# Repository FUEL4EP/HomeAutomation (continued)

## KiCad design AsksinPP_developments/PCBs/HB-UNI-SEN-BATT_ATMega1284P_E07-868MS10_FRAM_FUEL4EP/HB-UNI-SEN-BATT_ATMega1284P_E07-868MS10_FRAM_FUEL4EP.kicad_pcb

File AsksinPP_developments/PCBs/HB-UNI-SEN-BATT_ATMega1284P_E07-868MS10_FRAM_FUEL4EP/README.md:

# HB-UNI-SEN-BATT_ATMega1284P_E07-868MS10_FRAM_FUEL4EP ](https://creativecommons.org/licenses/by-nc-sa/4.0/)  

**Platine für DIY AsksinPP für**
- eingebauter SMD TQFP-44 [ATMega1284P](https://ww1.microchip.com/downloads/en/DeviceDoc/doc8059.pdf) mit 128kByte Programmspeicher, 16kByte SRAM, 4kByte EEPROM
- [eByte E07-868MS10 Sendemodul](https://www.rcscomponents.kiev.ua/datasheets/e07-868ms10_usermanual_en_v1_20.pdf)
- Bestückungsoption für [Waveshare ePaper Modul (1.54inch (B)](https://www.waveshare.com/product/1.54inch-e-paper-module.htm)
- Bestückungsoption für [TPS61221 Aufwärtswandler](https://www.ti.com/lit/ds/symlink/tps61221.pdf?ts=1634546965861&ref_url=https%253A%252F%252Fwww.ti.com%252Fproduct%252FTPS61221) bei NiMH Akkumulatorbetrieb
- Bestückungsoption für 2x 2Mbit (256k x 8Bit) SPI FRAM MB85RS2MTPF-G-JNERE2 für die Speicherung von Temperaturdaten für die online-Berechnung von gleitenden Mittelwerten bis zu einem Jahr (365 Tage)
- alle SMD Bausteine sind mit dem JLCPCB SMT Bestückungsservice kostengünstig und qualitativ hochwertig bestückbar, das ist also auch für Grobmotoriker wie mich gegeignet :-)

## Credits

- diese Platine ist ursprünglich von Alexander Reinerts Platine [HB-UNI-SEN-BATT](https://github.com/alexreinert/PCB/tree/master/HB-UNI-SEN-BATT) abgeleitet, aber in vielerlei Hinsicht verbessert
- vielen Dank an Alexander Reinert für die Vorarbeit.

## Platine Version 1.1 wurde nach Fertigung bei JLCPCB erfolgreich validiert

- Version 1.1 wurde entwickelt mit KiCAD 5.1.12  
- für KiCAD 6 wurde eine Migration auf Version 1.2 durchgeführt
- Prototyp Version 1.1 erfolgreich  bei JLCPCB gefertigt und validiert
- Software ist noch in Entwicklung, siehe unten
- Bilder der Prototyp-Platinen, die bei JLCPCB gefertigt wurden:

- die nicht SMD Bauteile müssen von Hand verlötet werden
- weitere Infos per PN bei [FUEL4EP](https://homematic-forum.de/forum/ucp.php?i=pm&mode=compose&u=20685) im Homematic Forum.

## Eigenschaften

- abgeleitet aus [HB-UNI-SEN-BATT](https://github.com/alexreinert/PCB/tree/master/HB-UNI-SEN-BATT)
- kompletter Datensatz für KiCAD 6 auf Github verfügbar::
    + 'git clone https://github.com/FUEL4EP/HomeAutomation.git' oder als [ZIP-Datei](https://github.com/FUEL4EP/HomeAutomation/archive/refs/heads/master.zip)
    + die Platinendaten sind dann unter 'HomeAutomation/AsksinPP_developments/PCBs/HB-UNI-SEN-BATT_ATMega1284P_E07-868MS10_FRAM_FUEL4EP' direkt mit KiCAD aufrufbar
- neue Eigenschaften:
    + SMD Bestückung, wo möglich
    + SMD TQFP-44 [ATMega1284P](https://ww1.microchip.com/downloads/en/DeviceDoc/doc8059.pdf) mit 128kByte Programmspeicher, 16kByte SRAM, 4kByte EEPROM
    + Bestückungsoption für [Waveshare ePaper Modul (1.54inch (B)](https://www.waveshare.com/product/1.54inch-e-paper-module.htm)
    + Bestückungsoption für [TPS61221 Aufwärtswandler](https://www.ti.com/lit/ds/symlink/tps61221.pdf?ts=1634546965861&ref_url=https%253A%252F%252Fwww.ti.com%252Fproduct%252FTPS61221) bei NiMH Akkumulatorbetrieb
    + Bestückungsoption für 2x 2Mbit (256k x 8Bit) SPI FRAM MB85RS2MTPF-G-JNERE2 für die Speicherung von Temperaturdaten für die online-Berechnung von gleitenden Mittelwerten bis zu einem Jahr (365 Tage)
    + alle SMD Bausteine sind mit dem JLCPCB SMT Bestückungsservice kostengünstig und qualitativ hochwertig bestückbar, das ist also auch für Grobmotoriker wie mich gegeignet :-)
    + Stiftleiste J10 mit Versorgungspannungen zum Gehäuseoberteil oder Akkulademodul
    + dedizierte passende Stiftleisten für verschiedene Sensoren / Sensorbreakouts
        * J6: SHT75, SHT85
        * J7: AHT15, AHT25
        * J8: AHT20+BMP280 Breakout (z.B. [eBay](https://www.ebay.de/itm/174883359464)
        * J9: BME280/BMP280 Breakout
        * J13: BME680 Breakout (Pimoroni)
    + Korrektur der Abstandfehlers bei einem Batteriehalter. Beim [HB-UNI-SEN-BATT](https://github.com/alexreinert/PCB/tree/master/HB-UNI-SEN-BATT) hat das schon mal gerne zu thermischen Ausfällen durch mechanische Spannungen geführt.
    + als Funkmodul wird das [eByte E07-868MS10 Sendemodul](https://www.rcscomponents.kiev.ua/datasheets/e07-868ms10_usermanual_en_v1_20.pdf) verwendet. Dieses ist qualitativ viel besser als die üblichen grünen noname 868 MHz Funkmodule.
    + das schafft Platz für eine 8-polige Stiftleiste J11 zum optionalen Anschluss eines [Waveshare ePaper Moduls (1.54inch (B)](https://www.waveshare.com/product/1.54inch-e-paper-module.htm). Der ATMega1284P hat auch genügend RAM für die Programmierung eines 200 Pixel x 200 Pixel e-Papermoduls.
    + JLCPCB BOM and CPL Dateien für SMT Service werden [bereitgestellt](./jlcpcb/production_files)
- Hinweis: der MB85RS2MTPF FRAM Speicher muss bei JLCPCB als [Vorbestellung von Bauteilen](https://support.jlcpcb.com/article/164-what-is-jlcpcb-parts-pre-order-service) vorab gekauft werden

### Benötigte Bauteile:

- bedingt durch die SMT Service von JLCPCB sind nur noch wenige Durchsteckbauteile von Hand zu verlöten:
* [eByte E07-868MS10 Sendemodul 868MHz](https://www.elecbee.com/de-24376-E07-868MS10-CC1101-Stamp-Hole-Antenna-IoT-UHF-1000m-868MHz-SPI-10dBm-Wireless-Transmitter-Transceiver-RF-Module) oder alternativ das [Elecbee CC1101 Wireless-Modul 868 MHz](https://www.elecbee.com/de-24507-CC1101-Wireless-Module-868MHz-Digital-Transmission-Receiving-Industrial-grade-RF-Communication-Transparent-Transmission) Modul
* e-Paper [Waveshare ePaper Moduls (1.54inch (B)](https://www.waveshare.com/product/1.54inch-e-paper-module.htm) (optional, Anschluss an J11)
* 2x Keystone 2460 Batteriehalter 1xAA
* Stiftleiste RM 1.27mm 1x8 Pin (für eByte E07-868MS10 Sendemodul 868MHz)
* Stiftleiste RM 2mm 1x8 Pin (für ePaper)
* Stiftleisten RM 2,54mm (nach Bedarf)
* IRLU024N (optional für Verpolungsschutz)
* Versorgung durch NiMH Akkumulatoren und Aufwärtswandler ist vorbereitet (JP2)
* Bestückungsoption Aufwärtswandler siehe [Schaltplan](Schematics/HB-UNI-SEN-BATT_ATMega1284P_E07-868MS10_FUEL4EP.pdf), unter KiCAD sind alle Referenzen eingetragen

### Aufbauhinweise

- es wird dringend angeraten, vor dem Einbau der I2C Sensoren durchzuführen
    + einen Frequenztest. Hier der Frequenztest für einen ATmega 1284p : [FreqTest_1284P.ino](../Supplements/FreqTest_1284P/FreqTest_1284P.ino)
    + einen Leckagetest. Hier der Leckagetest für einen ATmega 1284p : [SleepTest_1284P.ino](../Supplements/SleepTest_1284P/SleepTest_1284P.ino)
        + der Leckagestrom im Sleepmode sollte < 10 uA betragen

### Passende AsksinPP Projekte von FUEL4EP
- eine passende Arduino FRAM Bibliothek ist [hier](../../sketches/HB-UNI-Sensor1-THP_MA-AHT20_BMP280/Sensors/Fujitsu_MB85RS2MTPF_FRAM_circular_buffer.h)
	* diese FRAM Bibliothek wird beim Sketch [HB-UNI-Sensor1-THP_MA-AHT20_BMP280](https://github.com/FUEL4EP/HomeAutomation/tree/master/AsksinPP_developments/sketches/HB-UNI-Sensor1-THP_MA-AHT20_BMP280) verwendet
- THP Sensor mit gleitender Mittelwertbildung der gemessenen Temperatur über 24 Stunden, 1 Woche, 1 Monat und 1 Jahr:
	* [HB-UNI-Sensor1-THP_MA-AHT20_BMP280](https://github.com/FUEL4EP/HomeAutomation/tree/master/AsksinPP_developments/sketches/HB-UNI-Sensor1-THP_MA-AHT20_BMP280)
		* alle Funktionen sind erfolgreich getestet, das FRAM funktioniert
		* damit lassen sich lokale Klimaschwankungen gut erfassen
		* der Sensor läuft bereits seit mehreren Monaten
- [HB-UNI-Sensor1-AQ-BME680](https://github.com/FUEL4EP/HomeAutomation/tree/master/AsksinPP_developments/sketches/HB-UNI-Sensor1-AQ-BME680)
- [HB-UNI-Sensor1-AQ-BME680_KF](https://github.com/FUEL4EP/HomeAutomation/tree/master/AsksinPP_developments/sketches/HB-UNI-Sensor1-AQ-BME680_KF)
- [HB-UNI-Sensor1-AQ-BME680_KF_DEBUG](https://github.com/FUEL4EP/HomeAutomation/tree/master/AsksinPP_developments/sketches/HB-UNI-Sensor1-AQ-BME680_KF_DEBUG)
- [HB-UNI-Sensor1-RAD-AL53](https://github.com/FUEL4EP/HomeAutomation/tree/master/AsksinPP_developments/sketches/HB-UNI-Sensor1-RAD-AL53)
- [HB-UNI-Sensor1-THP-SHT85](https://github.com/FUEL4EP/HomeAutomation/tree/master/AsksinPP_developments/sketches/HB-UNI-Sensor1-THP-SHT85)
- [HB-UNI-Sensor1-THP-SHT45_BME280](https://github.com/FUEL4EP/HomeAutomation/tree/master/AsksinPP_developments/sketches/HB-UNI-Sensor1-THP-SHT45_BME280)

### Notwendige Änderung der Betriebsspannungsmessung in Sketchen
- da die Platine einen fest verdrahteten Spannungsteiler R7 und R8 für die Betriebsspannung / Akkuspannungsmessung verwendet, muss in Sketchen folgende Anpassung gegebenenfalls durchgeführt werden:

- nur notwendig, wenn die Akkuspannung / Betriebsspannung größer als 3,5 Volt ist ( 2x AA Alkaline Batterie)

- von bisher
```
// 1) Standard: tmBattery, UBatt = Betriebsspannung AVR
#define BAT_SENSOR tmBattery
```
- nach
```
// 2) für StepUp/StepDown: tmBatteryResDiv, sense pin PA0 (=pin 37), activation pin PB3 (=pin 43) , Faktor = Rges/Rlow*1000, z.B. (100kOhm+47kOhm/100kOhm), Faktor (147k)/(100k)*1000 = 1470 (ATMega1284P)
// start with Faktor = 1470
// check in serial monitor the reported V2='accumulator voltage(MCU ADC) (x1000.0)' and compare with the reported V1='accumulator batteries voltage (x1000.0)'
// calculate voltage correction factor V1/V2
// calculate total Faktor = 1470 * V2/V1 = 1470 * 3141 / 3157 = 1463
#define BAT_SENSOR tmBatteryResDiv<A0, PB3, 1463>
```
- zur Berechnung von Faktor in tmBatteryResDiv wird ein Libreoffice Calc Sheet [tmBattery_tmBatteryResDiv_calculator.ods](../../tools/tmBattery_tmBatteryResDiv_calculator.ods) zur Verfügung gestellt
- in der Version 1.0 war R8 = 200kOhm, daher Faktor = 3000 (ohne Kalibrierung)
- in der Version 1.1 ist R8 = 47kOhm, daher Faktor = 1470 (ohne Kalibrierung)
### Anschluss eines FTDI Debuggers

- zum Anschluss eines FTDI Debuggers an die 6-polige Stiftleiste J12 bitte ein [6 Pin Dupontkabel 2.54mm Buchse-Buchse 20 cm](https://www.roboter-bausatz.de/p/6-pin-dupontkabel-2.54mm-buchse-buchse-20-cm) verwenden

### Passendes Gehäuse
* Camdenboss CBRS01SWH und CBRS01VWH
* oder [Gehäuse HB-UNI-SEN-BATT snap in V2 von wpatrick](https://www.thingiverse.com/thing:3540481) für 3D-Druck
* bei Einbau eines e-Paper Moduls muss das Gehäuseoberteil angepasst werden (noch zu tun)

### Hinweise
* Achtung: Kein Überspannungschutz vorhanden
* der Verpolungsschutz ist optional. Dafür Bauteil Q1 (IRLU024N) und R3 (100KOhm Widerstand) bestücken. Alternativ JP1 auf der Platinenrückseite brücken um ohne Verpolungsschutz zu arbeiten.
 * bei der Nutzung des JLCPCB SMT Bestückungsservice ist darauf zu achten, dass **alle** benötigten SMD Bauteile als im Lager **verfügbar** angezeigt werden. Sonst bitte **NICHT** bestellen! Gegebenenfalls müssen für die SMD-Widerstände äquivalente Widerstände von anderen Herstellern über die Suchfunktion ausgewählt werden.
 
## passende DIY AsksinPP Funkmodule 868,3 MHz für die Fertigung bei JLCPCB
- als DIY-Ersatz für das eByte E07 868M10S Funkmodul stehen zur Verfügung:
	-  [CC1101_868MHz_RF_Modul_FUEL4EP](https://github.com/FUEL4EP/HomeAutomation/tree/master/AsksinPP_developments/PCBs/CC1101_868MHz_RF_Modul_FUEL4EP) mit Drahtantenne
	- [CC1101_868MHz_UFL_RF_Modul_FUEL4EP](https://github.com/FUEL4EP/HomeAutomation/tree/master/AsksinPP_developments/PCBs/CC1101_868MHz_UFL_RF_Modul_FUEL4EP) mit U.FL Antennenbuchse
* alternativ für das Funkmodul eByte E07 868M10S kann der Adapter [Adapter_EByte_E07_900MM10S_to_Ebyte_E07_868MS10_FUEL4EP](https://github.com/FUEL4EP/HomeAutomation/tree/master/AsksinPP_developments/PCBs/Adapter_EByte_E07_900MM10S_to_Ebyte_E07_868MS10_FUEL4EP) bestückt mit einem Funkmodul eByte E07 900MM10S verwendet werden
	
## passende DIY I2C-Sensormodule für die Fertigung bei JLCPCB
- als DIY-Ersatz für kommerzielle Sensormodule stehen folgende passende Adapterplatinen zur Verfügung:
	- [I2C_Module_BME280_FUEL4EP](https://github.com/FUEL4EP/HomeAutomation/tree/master/AsksinPP_developments/PCBs/I2C_Module_BME280_FUEL4EP)
	- [I2C_Module_BME680_FUEL4EP](https://github.com/FUEL4EP/HomeAutomation/tree/master/AsksinPP_developments/PCBs/I2C_Module_BME680_FUEL4EP)
	- [I2C_Module_SHT85_BME280_FUEL4EP](https://github.com/FUEL4EP/HomeAutomation/tree/master/AsksinPP_developments/PCBs/I2C_Module_SHT85_BME280_FUEL4EP)
	- [I2C_Module_SHT45_BME280_FUEL4EP](https://github.com/FUEL4EP/HomeAutomation/tree/master/AsksinPP_developments/PCBs/I2C_Module_SHT45_BME280_FUEL4EP)
	- [4Bit_I2C_Port_Expander_Module_FUEL4EP](https://github.com/FUEL4EP/HomeAutomation/tree/master/AsksinPP_developments/PCBs/4Bit_I2C_Port_Expander_Module_FUEL4EP)

## Disclaimer

-   die Nutzung der hier veröffentlichten Inhalte erfolgt vollständig auf eigenes Risiko und ohne jede Gewähr.

## Versionsverlauf

-	V1.1 10. Jan 2022: R8 auf 47kOhm geändert, zusätzliche Aufdrucktexte
-   V1.1 10. Mai 2023: Prototypen von JLCPCB verfügbar, Systemvalidierung und Softwareentwicklung muss noch gemacht werden
-   V1.2 16. Jul 2023: Migration der Datenbasen zu KiCAD 6; als Induktivität    	                     für den Aufwärtswandler wird nun LQH3NPN4R7MM0L von
                         Murata Electronics verwendet, die bei JLCPCB bestellbar ist  (eventuell ist eine Vorbestellung notwendig) 
-   V1.3 14. Jul 2023: KiCAD 6 bedingte Verbesserungen der Datenbasis
-   V1.4 15. Aug 2023: Fix of EN pin of TPS61221 boost converter (must be tied to VIN)
-   S V1.5 17. Feb 2024: Fix of LCSC-Nummer von R7 (Fehler bei KiCAD 6 Migration) und KiCAD 6-Bibliothekspfad
-   S V1.6 26. Sep 2024: Migration auf KiCAD 8; Fix of LCSC-Nummern (R2,R4,R5)
-   L V1.5 26. Sep 2024: Migration auf KiCAD 8; Fix of LCSC-Nummern (R2,R4,R5) 
- KiCad Schaltplan-Editor Version: 8.0.5-8.0.5-0~ubuntu22.04.1, release build unter Kubuntu22.04.1
- KiCad Leiterplatteneditor Version: 8.0.5-8.0.5-0~ubuntu22.04.1, release build unter Kubuntu22.04.1 1.
- PCB Version 1.5
- Schematics  1.6

## Lizenz 

**Creative Commons BY-NC-SA**<br>
Give Credit, NonCommercial, ShareAlike

<br />This work is licensed under a <a rel="license" href="http://creativecommons.org/licenses/by-nc-sa/4.0/">Creative Commons Attribution-NonCommercial-ShareAlike 4.0 International License</a>.

-EOF

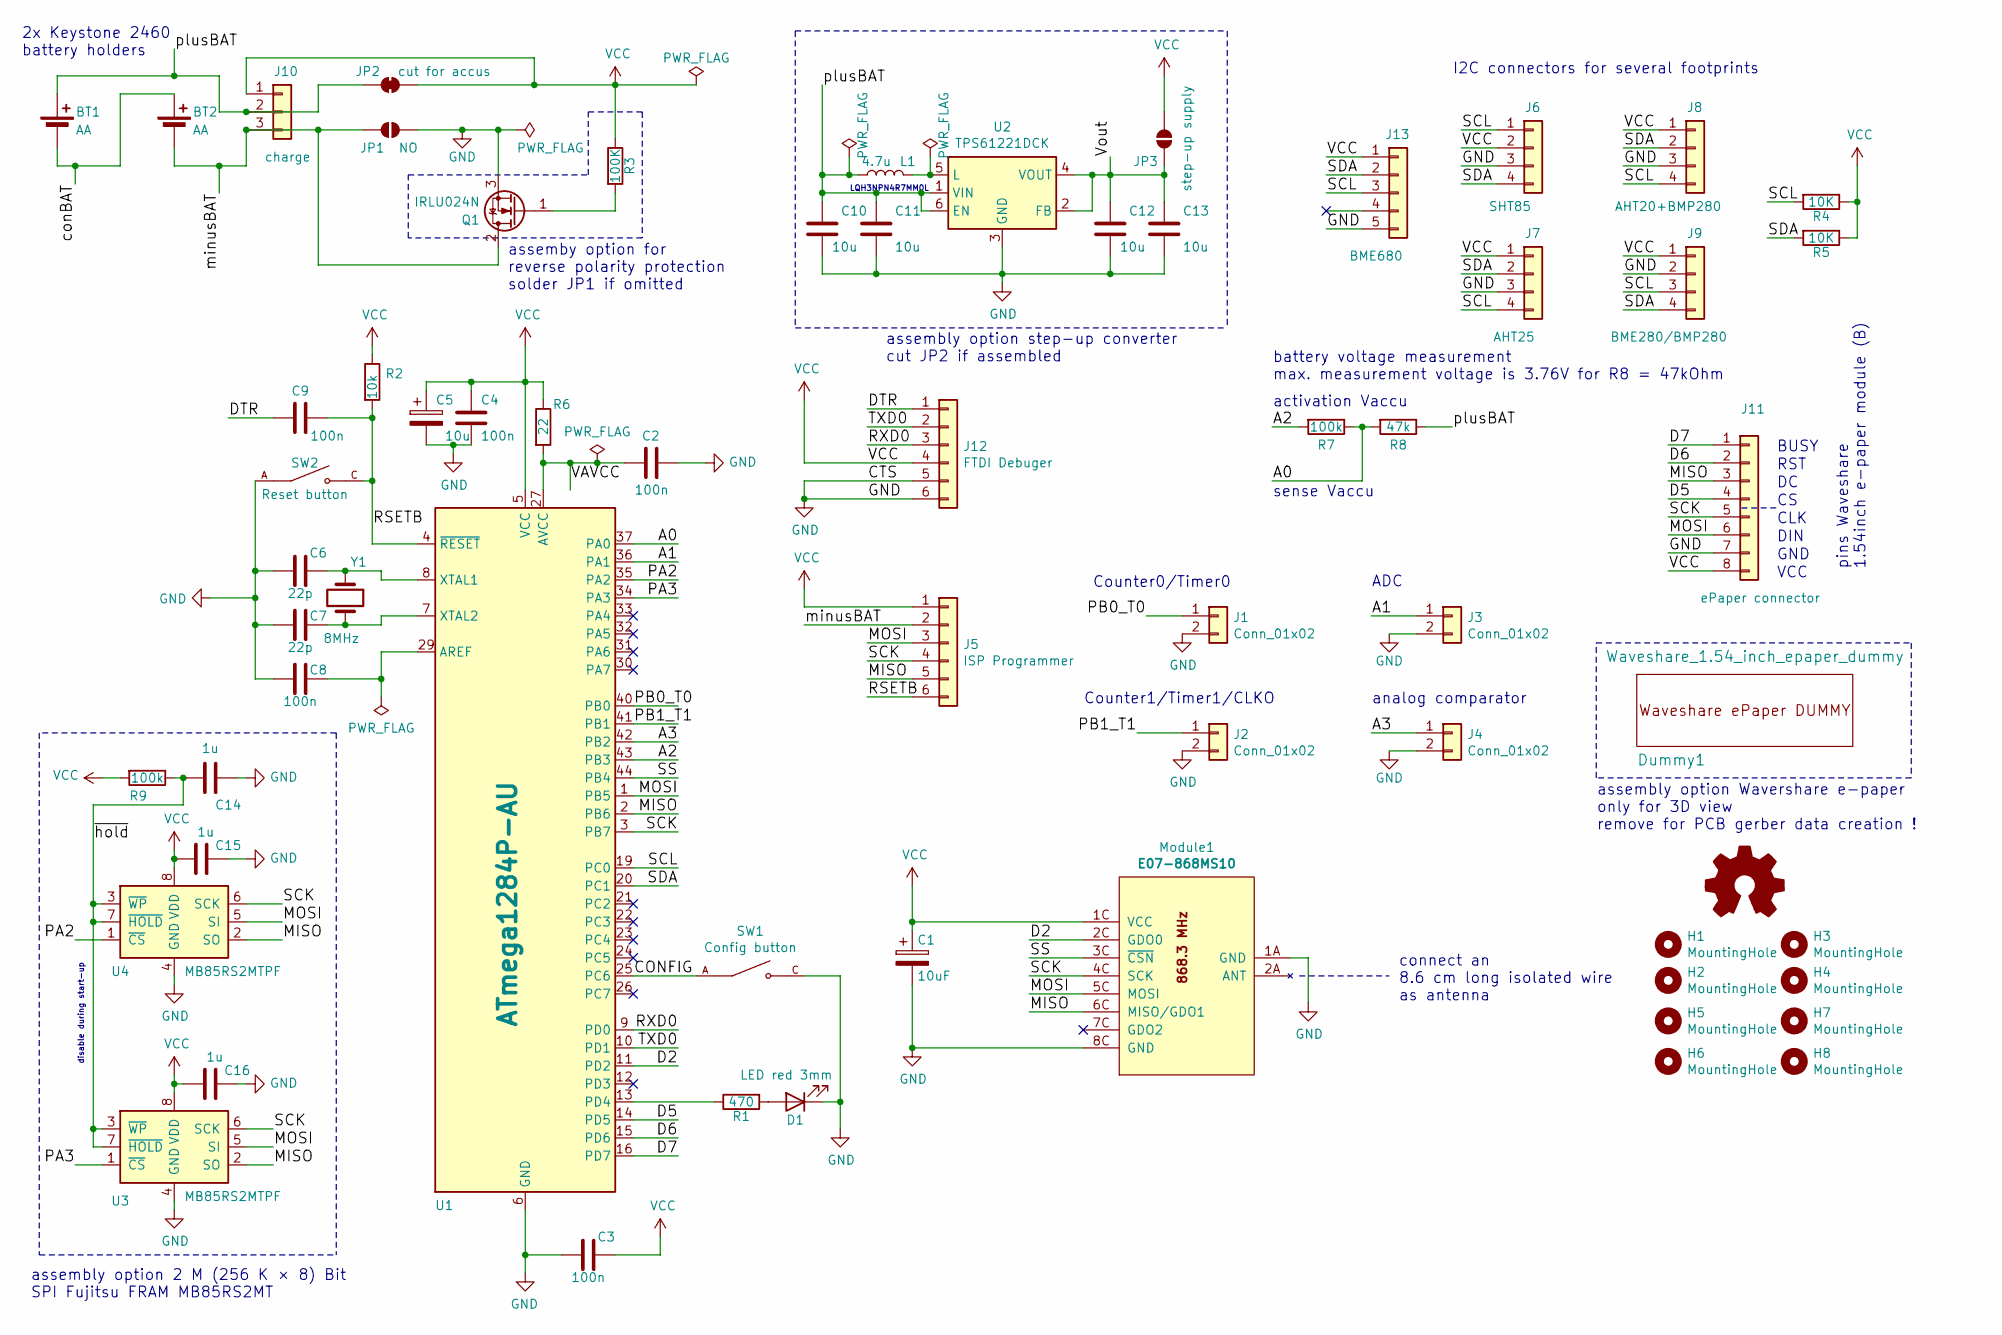
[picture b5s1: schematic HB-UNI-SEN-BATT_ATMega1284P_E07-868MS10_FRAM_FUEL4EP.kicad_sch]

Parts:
BT1, BT2: AA; BatteryHolder_Keystone_2460_1xAA
C1: 10uF; C_1206_3216Metric_Pad1.33x1.80mm_HandSolder; LCSC C7171
C2, C3, C4, C8, C9: 100n; C_0805_2012Metric; LCSC C28233
C5: 10u; C_1206_3216Metric_Pad1.33x1.80mm_HandSolder; LCSC C7171
C6, C7: 22p; C_0805_2012Metric; LCSC C1804
C10, C11, C12, C13: 10u; C_0805_2012Metric; LCSC C15850
C14, C15, C16: 1u; C_0805_2012Metric; LCSC C28323
D1: LED red 3mm; LED_0805_2012Metric_Pad1.15x1.40mm_HandSolder; LCSC C84256
Dummy1: Waveshare_1.54_inch_epaper_dummy; Waveshare_ePaper_module
H1, H2, H3, H4: MountingHole; MountingHole_2.2mm_M2_Pad_Via
H5, H6, H7, H8: MountingHole; ePaper_MountingHole_M5
J1, J2, J3, J4: Conn_01x02; PinHeader_1x02_P2.54mm_Vertical
J5: ISP Programmer; PinHeader_1x06_P2.54mm_Vertical
J6: SHT85; PinHeader_1x04_P1.27mm_Vertical
J7: AHT25; PinHeader_1x04_P1.27mm_Vertical
J8: AHT20+BMP280; PinHeader_1x04_P2.54mm_Vertical
J9: BME280/BMP280; PinHeader_1x04_P2.54mm_Vertical
J10: charge; PinHeader_1x03_P2.54mm_Vertical
J11: ePaper connector; PinPads_1x08_P2.00mm_Vertical
J12: FTDI Debuger; PinHeader_1x06_P2.54mm_Vertical
J13: BME680; PinHeader_1x05_P2.54mm_Vertical
JP1: NO; SolderJumper-2_P1.3mm_Open_Pad1.0x1.5mm
JP2: cut for accus; SolderJumper-2_P1.3mm_Bridged_Pad1.0x1.5mm
JP3: step-up supply; SolderJumper-2_P1.3mm_Open_Pad1.0x1.5mm
L1: 4.7u; FUEL4EP_Inductor_SMD_1; LCSC C86077
LOGO1: Logo_Open_Hardware_Small; CC-BY-ND-SA
Module1: E07-868MS10; eByte_E07-868MS10
Q1: IRLU024N; TO-251-3_Vertical; LCSC C558184
R1: 470; R_0805_2012Metric_Pad1.20x1.40mm_HandSolder; LCSC C17710
R2: 10k; R_0805_2012Metric_Pad1.20x1.40mm_HandSolder; LCSC C17414
R3: 100K; R_0805_2012Metric_Pad1.20x1.40mm_HandSolder; LCSC C340475
R4, R5: 10K; R_0805_2012Metric_Pad1.20x1.40mm_HandSolder; LCSC C17414
R6: 22; R_0805_2012Metric_Pad1.20x1.40mm_HandSolder; LCSC C23345
R7: 100k; R_0805_2012Metric_Pad1.20x1.40mm_HandSolder; LCSC C149504
R8: 47k; R_0805_2012Metric_Pad1.20x1.40mm_HandSolder; LCSC C17713
R9: 100k; R_0805_2012Metric_Pad1.20x1.40mm_HandSolder; LCSC C340475
SW1: Config button; SW_TS-1187A-B-A-B; PARTREV A0; LCSC C318884
SW2: Reset button; SW_TS-1187A-B-A-B; PARTREV A0; LCSC C318884
U1: ATmega1284P-AU; TQFP-44_10x10mm_P0.8mm; LCSC C33575
U2: TPS61221DCK; Texas_R-PDSO-G6; LCSC C37055
U3, U4: MB85RS2MTPF; SOP-8_5.28x5.23mm_P1.27mm; LCSC C126734
Y1: 8MHz; Crystal_SMD_5032-2Pin_5.0x3.2mm_HandSoldering; LCSC C115962

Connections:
/A0: R7.1, R8.2, U1.37 (PA0)
/A1: J3.1, U1.36 (PA1)
/A2: R7.2, U1.43 (PB3)
/A3: J4.1, U1.42 (PB2)
/CONFIG: SW1.A, SW1.B (e), U1.25 (PC6)
/D2: Module1.2C (GDO0), U1.11 (PD2)
/D5: J11.4, U1.14 (PD5)
/D6: J11.2, U1.15 (PD6)
/D7: J11.1, U1.16 (PD7)
/DTR: C9.2, J12.1
/MISO: J5.5, J11.3, Module1.6C (MISO/GDO1), U1.2 (PB6), U3.2 (SO), U4.2 (SO)
/MOSI: J5.3, J11.6, Module1.5C (MOSI), U1.1 (PB5), U3.5 (SI), U4.5 (SI)
/PA2: U1.35 (PA2), U4.1 (~CS)
/PA3: U1.34 (PA3), U3.1 (~CS)
/PB0_T0: J1.1, U1.40 (PB0)
/PB1_T1: J2.1, U1.41 (PB1)
/RSETB: C9.1, J5.6, R2.2, SW2.C, SW2.D, U1.4 (~RESET)
/RXD0: J12.3, U1.9 (PD0)
/SCK: J5.4, J11.5, Module1.4C (SCK), U1.3 (PB7), U3.6 (SCK), U4.6 (SCK)
/SCL: J6.1, J7.4, J8.4, J9.3, J13.3, R4.2, U1.19 (PC0)
/SDA: J6.4, J7.2, J8.2, J9.4, J13.2, R5.2, U1.20 (PC1)
/SS: Module1.3C (~CSN), U1.44 (PB4)
/TXD0: J12.2, U1.10 (PD1)
/VAVCC: C2.2, R6.2, U1.27 (AVCC)
/Vout: C12.1, C13.1, JP3.1 (A), U2.2 (FB), U2.4 (VOUT)
/conBAT: BT1.2 (-), BT2.1 (+)
/minusBAT: BT2.2 (-), J5.2, J10.3, JP1.1 (A), Q1.2 (D)
/plusBAT: BT1.1 (+), C10.1, C11.1, J10.2, JP2.1 (A), L1.1, R8.1, U2.1 (VIN), U2.6 (EN)
/~hold: C14.1, R9.1, U3.3 (~WP), U3.7 (~HOLD), U4.3 (~WP), U4.7 (~HOLD)
GND: C1.2, C2.1, C3.2, C4.2, C5.2, C6.2, C7.2, C8.2, C10.2, C11.2, C12.2, C13.2, C14.2, C15.2, C16.2, D1.1 (K), J1.2, J2.2, J3.2, J4.2, J6.3, J7.3, J8.3, J9.2, J11.7, J12.5, J12.6, J13.5, JP1.2 (B), Module1.1A (GND), Module1.8C (GND), Q1.3 (S), SW1.C, SW1.D, SW2.A, SW2.B (e), U1.6 (GND), U1.18 (GND), U1.28 (GND), U1.39 (GND), U2.3 (GND), U3.4 (GND), U4.4 (GND)
unnamed: D1.2 (A), R1.2
unnamed: Q1.1 (G), R3.2
unnamed: C8.1, U1.29 (AREF)
unnamed: R1.1, U1.13 (PD4)
unnamed: C6.1, U1.8 (XTAL1), Y1.1
unnamed: C7.1, U1.7 (XTAL2), Y1.2
unnamed: L1.2, U2.5 (L)
VCC: C1.1, C3.1, C4.1, C5.1, C15.1, C16.1, J5.1, J6.2, J7.1, J8.1, J9.1, J10.1, J11.8, J12.4, J13.1, JP2.2 (B), JP3.2 (B), Module1.1C (VCC), R2.1, R3.1, R4.1, R5.1, R6.1, R9.2, U1.5 (VCC), U1.17 (VCC), U1.38 (VCC), U3.8 (VDD), U4.8 (VDD)

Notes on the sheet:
assembly option Wavershare e-paper only for 3D view remove for PCB gerber data creation !
pins Waveshare 1.54inch e-paper module (B)
activation Vaccu
ADC
assembly option step-up converter cut JP2 if assembled
RST
disable during start-up
Counter1/Timer1/CLKO
I2C connectors for several footprints
2x Keystone 2460 battery holders
CLK
connect an 8.6 cm long isolated wire as antenna
DIN
battery voltage measurement max. measurement voltage is 3.76V for R8 = 47kOhm
Counter0/Timer0
assemby option for reverse polarity protection solder JP1 if omitted
sense Vaccu
BUSY
assembly option 2 M (256 K × 8) Bit SPI Fujitsu FRAM MB85RS2MT
analog comparator
LQH3NPN4R7MM0L
VCC
GND

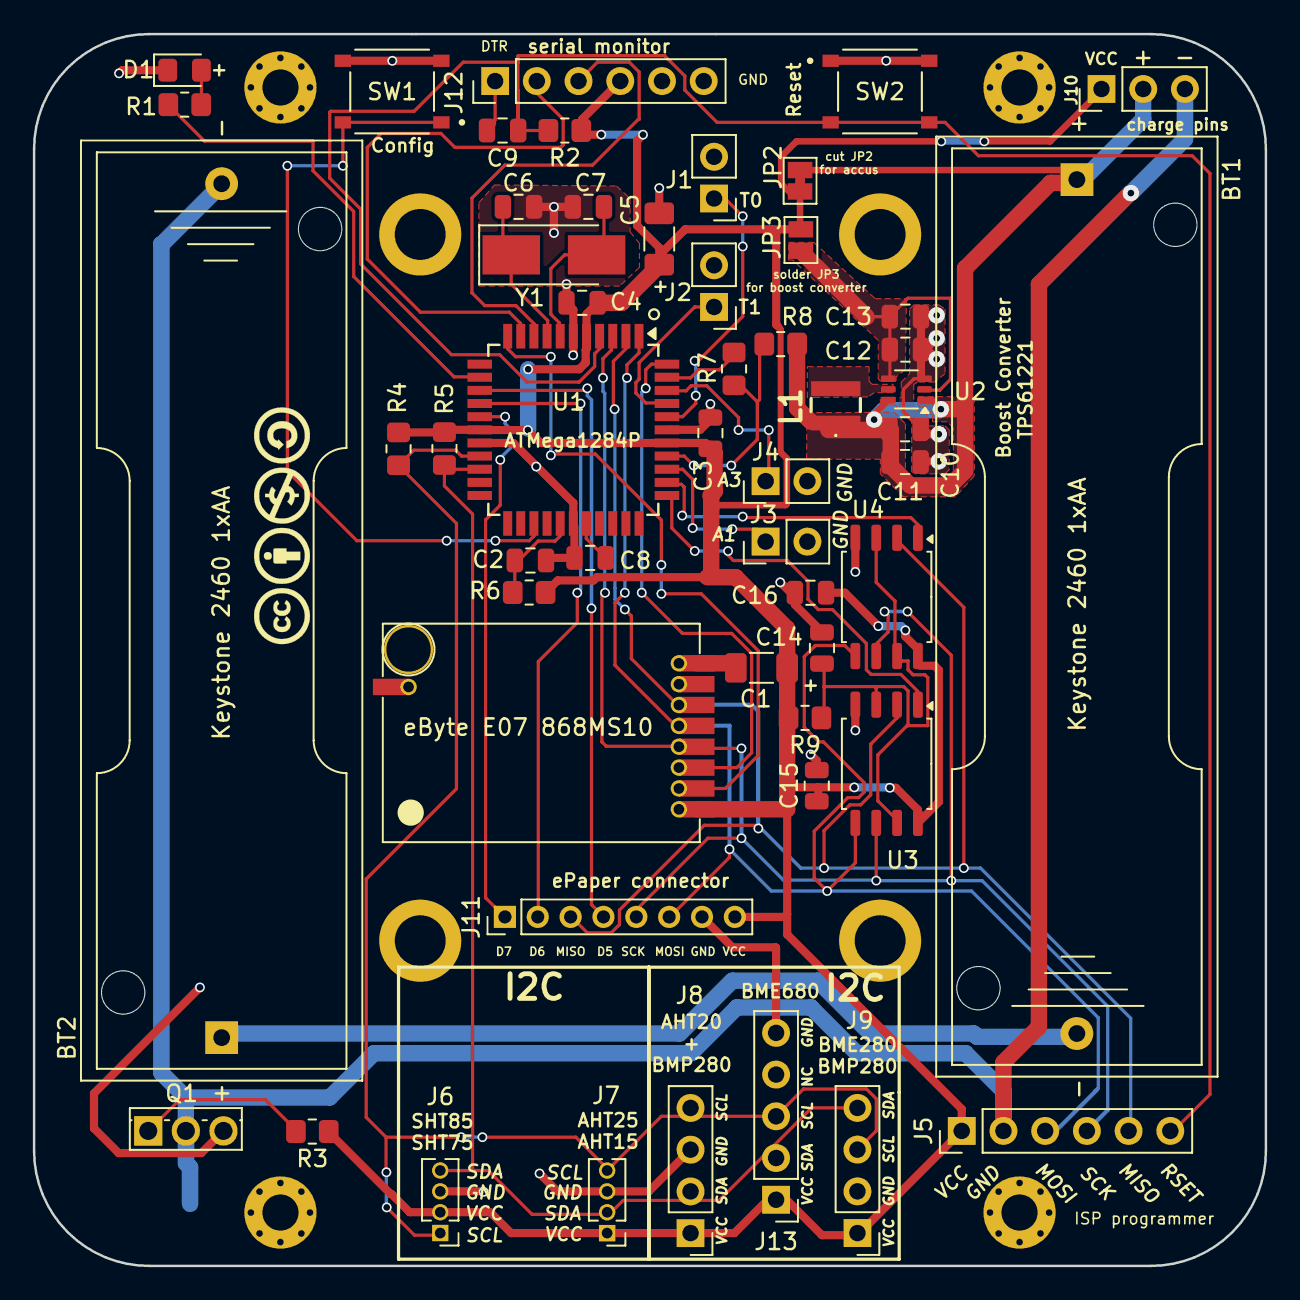
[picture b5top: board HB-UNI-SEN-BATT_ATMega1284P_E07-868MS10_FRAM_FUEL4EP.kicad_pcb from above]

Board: 2 copper layers, 75.0 x 75.0 mm, 63 parts (0 on the bottom side), 38 nets.

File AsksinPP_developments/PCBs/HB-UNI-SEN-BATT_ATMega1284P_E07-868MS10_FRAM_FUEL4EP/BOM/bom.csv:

"Comment","Designator","Footprint","LCSC Part Number"
"10uF Polarized capacitor","C1","=""CASE-A_3216""","C7171"
"100n Unpolarized capacitor","C2,C3,C4,C8,C9","=""0805""","C28233"
"10u Polarized capacitor","C5","=""CASE-A_3216""","C7171"
"22p Unpolarized capacitor","C6,C7","=""0805""","C1804"
"10u Unpolarized capacitor","C10,C11,C12,C13","=""0805""","C15850"
"1u Unpolarized capacitor","C14,C15,C16","=""0805""","C15849"
"LED red 3mm Light emitting diode","D1","=""LED_0805""","C84256"
"IRLU024N N-MOSFET transistor, gate/drain/source","Q1","=""TO-251""","C558184"
"470 Resistor","R1","=""0805""","C17710"
"10k Resistor","R2","=""0805""","C17733"
"100K Resistor","R3","=""R0805""","C101406"
"10K Resistor","R4,R5","=""R0805""","C101405"
"22 Resistor","R6","=""0603""","C23345"
"100k Resistor","R7,R9","=""R0805""","C101406"
"47k Resistor","R8","=""0805""","C17713"
"Config button ","SW1","=""SMD-SW-4_5.1x5.1x1.5""","C318884"
"Reset button ","SW2","=""SMD-SW-4_5.1x5.1x1.5""","C318884"
"ATmega1284P-AU 20MHz, 128kB Flash, 16kB SRAM, 4kB EEPROM, JTAG, TQFP-44","U1","=""TQFP-44_10.0x10.0x0.8P""","C33575"
"TPS61221DCK 400 mA Step-Up Converter, Fixed 3.3V Output Voltage, 0.7-5.5V Input Voltage, SC-70","U2","=""SOT-363""","C37055"
"MB85RS2MTPF Memory FRAM 2 MBit (256 K ×  8) Bit SPI MB85RS2MT","U3,U4","=""SOP-8_5.2x5.3x1.27P""","C126734"
"8MHz Two pin crystal","Y1","=""SMD-5032_2P""","C115962"
